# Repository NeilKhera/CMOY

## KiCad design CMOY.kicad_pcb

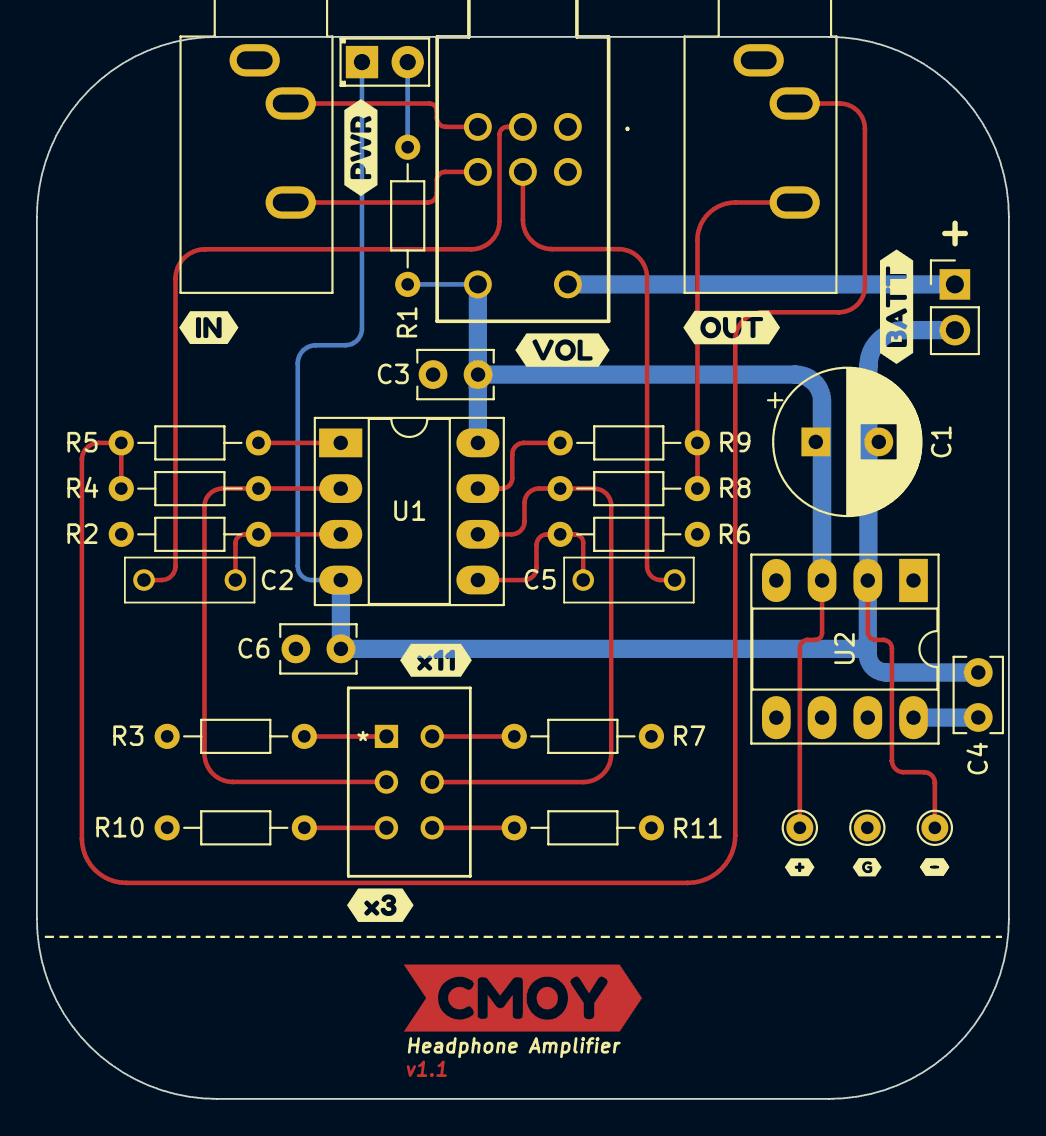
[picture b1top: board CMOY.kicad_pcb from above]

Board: 4 copper layers, 54.0 x 59.0 mm, 40 parts (0 on the bottom side), 22 nets.

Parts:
+: +4.5V; TestPoint_THTPad_D1.5mm_Drill0.7mm
-: -4.5V; TestPoint_THTPad_D1.5mm_Drill0.7mm
BT1: 9V; PinHeader_1x02_P2.54mm_Vertical
C1: 220uF; CP_Radial_D8.0mm_P3.50mm
C2, C5: 0.1uF; BFC237022104
C3, C6: 10nF; C_Rect_L4.0mm_W2.5mm_P2.50mm
C4: 1uF; C_Rect_L4.0mm_W2.5mm_P2.50mm
D1: LED_Small; LED_D2.0mm_W4.8mm_H2.5mm_FlatTop
G: GND; TestPoint_THTPad_D1.5mm_Drill0.7mm
J2, J2#2: SJ1-3533; Jack_3.5mm_CUI_SJ1-3533NG_Horizontal
R1: 4.7K; R_Axial_DIN0204_L3.6mm_D1.6mm_P7.62mm_Horizontal
R2, R6: 100K; R_Axial_DIN0204_L3.6mm_D1.6mm_P7.62mm_Horizontal
R3, R7: 1K; R_Axial_DIN0204_L3.6mm_D1.6mm_P7.62mm_Horizontal
R4, R8: 10K; R_Axial_DIN0204_L3.6mm_D1.6mm_P7.62mm_Horizontal
R5, R9: 47R; R_Axial_DIN0204_L3.6mm_D1.6mm_P7.62mm_Horizontal
R10, R11: 5K; R_Axial_DIN0204_L3.6mm_D1.6mm_P7.62mm_Horizontal
RV1: RK0971221Z05
SW1: SS22SDP2; SS22SDP2_NKK
U1: OPA2132PA; DIP-8_W7.62mm_Socket_LongPads
U2: TLE2426xD; DIP-8_W7.62mm_Socket_LongPads
kibuzzard-6510B7DC: G***; kibuzzard-6510B7DC
kibuzzard-6510B65E: G***; kibuzzard-6510B65E
kibuzzard-6510B680: G***; kibuzzard-6510B680
kibuzzard-6510B696: G***; kibuzzard-6510B696
kibuzzard-6510B935: G***; kibuzzard-6510B935
kibuzzard-6524AA5F, kibuzzard-6524AA5F#2: G***; kibuzzard-6524AA5F
kibuzzard-6524AA66: G***; kibuzzard-6524AA66
kibuzzard-6524AA99: G***; kibuzzard-6524AA99
kibuzzard-6524C2C1: G***; kibuzzard-6524C2C1
kibuzzard-6524C34B: G***; kibuzzard-6524C34B
kibuzzard-6524C337: G***; kibuzzard-6524C337

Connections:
+VSW: +.1, C1.1, C3.1, R1.1, RV1.8 (B), U1.8 (V+), U2.3 (IN)
-VSW: -.1, BT1.2 (-), C1.2, C4.2, C6.1, D1.1 (K), U1.4 (V-), U2.2 (COMMON)
/In_L: J2.T, RV1.3
/In_R: J2.R, RV1.6
/Out_L: J2#2.T, R4.2, R5.2
/Out_R: J2#2.R, R8.2, R9.2
GND: C3.2, C6.2, G.1, J2.S, J2#2.S, R2.2, R3.2, R6.2, R7.2, R10.2, R11.2, RV1.1, RV1.4, U2.1 (OUT)
unnamed: BT1.1 (+), RV1.7 (A)
unnamed: C2.1, RV1.2
unnamed: C5.1, RV1.5
unnamed: D1.2 (A), R1.2
unnamed: R5.1, U1.1
unnamed: R9.1, U1.7
unnamed: R3.1, SW1.1 (A)
unnamed: R4.1, SW1.2 (B), U1.2 (-)
unnamed: R10.1, SW1.3 (C)
unnamed: R7.1, SW1.4 (A)
unnamed: R8.1, SW1.5 (B), U1.6 (-)
unnamed: R11.1, SW1.6 (C)
unnamed: C2.2, R2.1, U1.3 (+)
unnamed: C5.2, R6.1, U1.5 (+)
unnamed: C4.1, U2.8 (NOISE_REDUCTION)

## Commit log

2024-05-03 Added .gitignore
2024-05-03 File upload
2024-05-03 Update to KiCad 8
